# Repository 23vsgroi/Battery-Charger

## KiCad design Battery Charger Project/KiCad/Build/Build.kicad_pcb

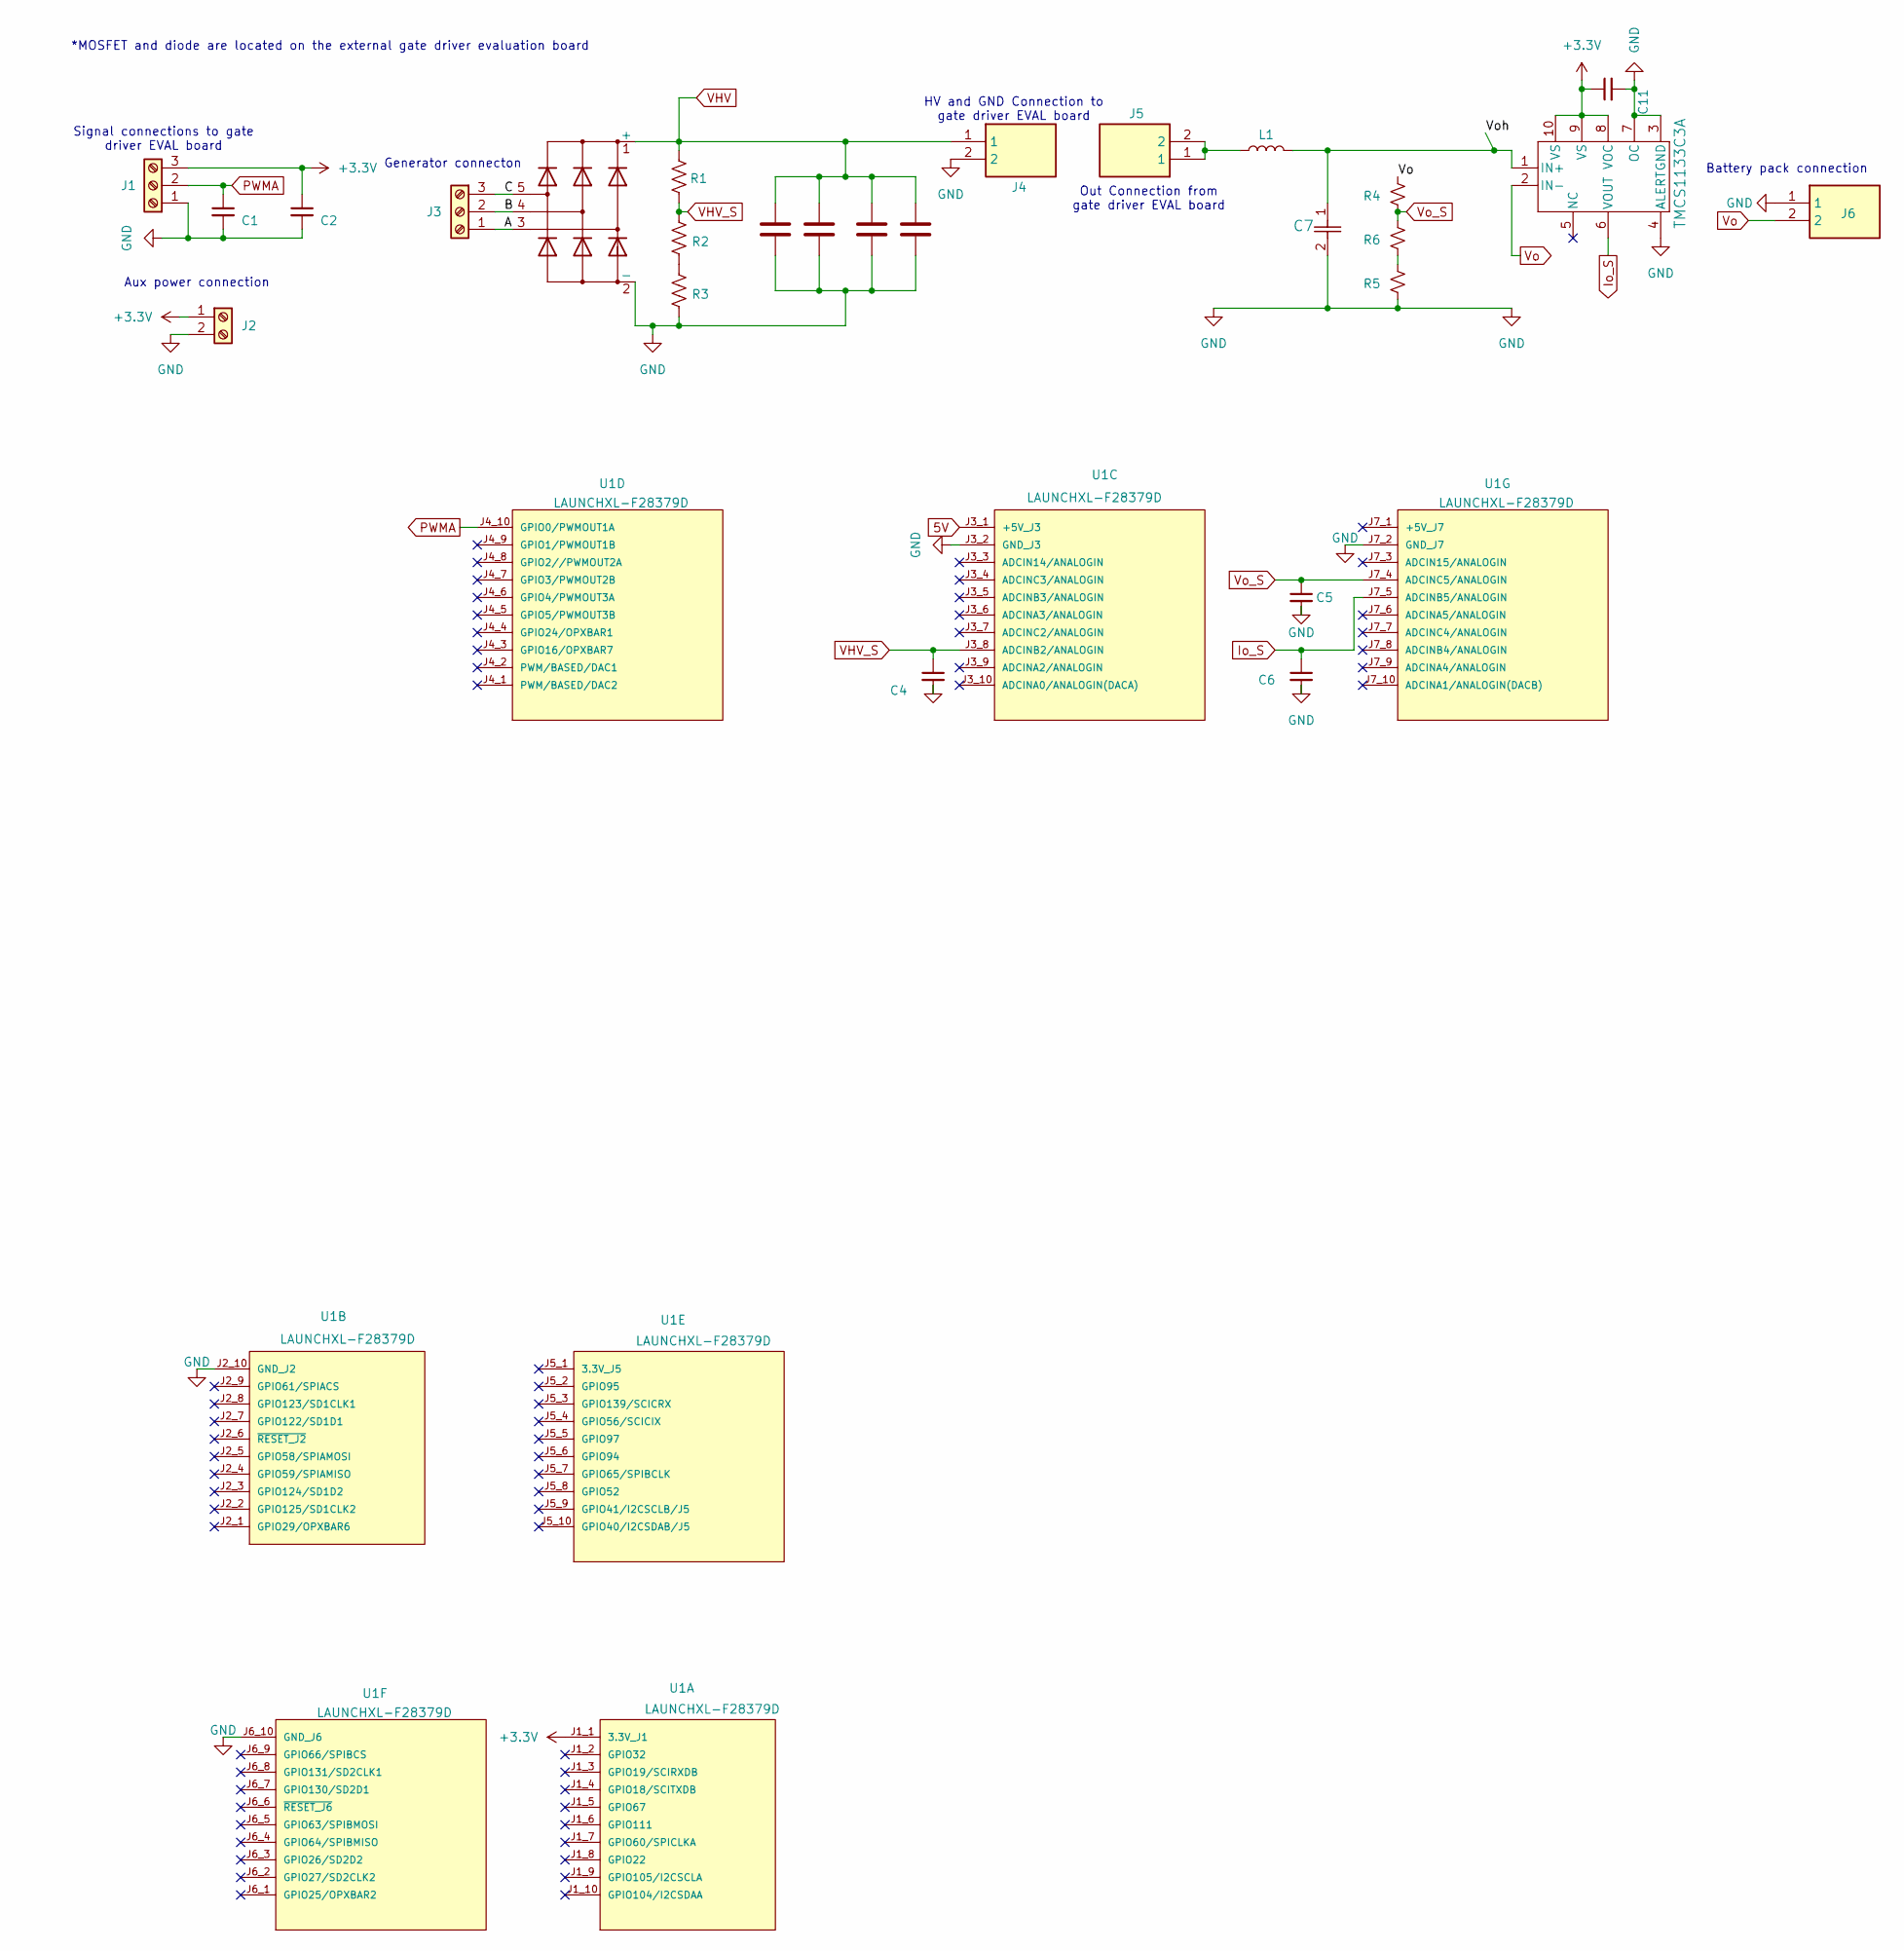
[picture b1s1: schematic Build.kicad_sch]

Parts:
C1, C2, C4, C5, C6, C11: C_Small; C_0805_2012Metric_Pad1.18x1.45mm_HandSolder
C3, C8, C9, C10: CAP_A30_NCH
C7: LLS2V821MELC; CAP_PAN_5X11_PAN
D1: DNA40U2200GU; DPF30U200FC
J1: Screw_Terminal_01x03; CONN3_284391-3_TEC
J2: Screw_Terminal_01x02; CONN2_284391-2_TEC
J3: Screw_Terminal_01x03; CONN_1935174_PXC
J4, J5, J6: 726386-2; CONN2_284391-2_TEC; Mouser Part Number 571-726386-2
L1: L; LC200-0185
R1: 300K; R_2010_5025Metric
R2: 6490; R_2010_5025Metric
R3: 36; R_2010_5025Metric
R4: 5K; R_2010_5025Metric
R5, R6: 680; R_2010_5025Metric
U1: LAUNCHXL-F28379D; PARTREV 2.0
U2: TMCS1133C3A; TMCS1133C5AQDVGR

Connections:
5V: U1.J3_1 (+5V_J3)
+3.3V: C2.1, C11.1, J1.3, J2.1, U1.J1_1 (3.3V_J1), U2.8 (VOC), U2.9 (VS), U2.10 (VS)
/A: D1.3, J3.1
/B: D1.4, J3.2
/C: D1.5, J3.3
/Voh: C7.1, L1.2, U2.1 (IN+)
GND: C1.2, C2.2, C3.2, C4.2, C5.2, C6.2, C7.2, C8.2, C9.2, C10.2, C11.2, D1.2 (-), J1.1, J2.2, J4.2, J6.1, R3.2, R5.2, U1.J2_10 (GND_J2), U1.J3_2 (GND_J3), U1.J6_10 (GND_J6), U1.J7_2 (GND_J7), U2.3 (GND), U2.4 (ALERT), U2.7 (OC)
Io_S: C6.1, U1.J7_5 (ADCINB5/ANALOGIN), U2.6 (VOUT)
unnamed: J5.1, J5.2, L1.1
unnamed: R2.2, R3.1
unnamed: R5.1, R6.2
PWMA: C1.1, J1.2, U1.J4_10 (GPIO0/PWMOUT1A)
VHV: C3.1, C8.1, C9.1, C10.1, D1.1 (+), J4.1, R1.1
VHV_S: C4.1, R1.2, R2.1, U1.J3_8 (ADCINB2/ANALOGIN)
Vo: J6.2, R4.1, U2.2 (IN-)
Vo_S: C5.1, R4.2, R6.1, U1.J7_4 (ADCINC5/ANALOGIN)

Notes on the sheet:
Aux power connection
Signal connections to gate driver EVAL board
Out Connection from gate driver EVAL board
Generator connecton
*MOSFET and diode are located on the external gate driver evaluation board
HV and GND Connection to gate driver EVAL board
Battery pack connection

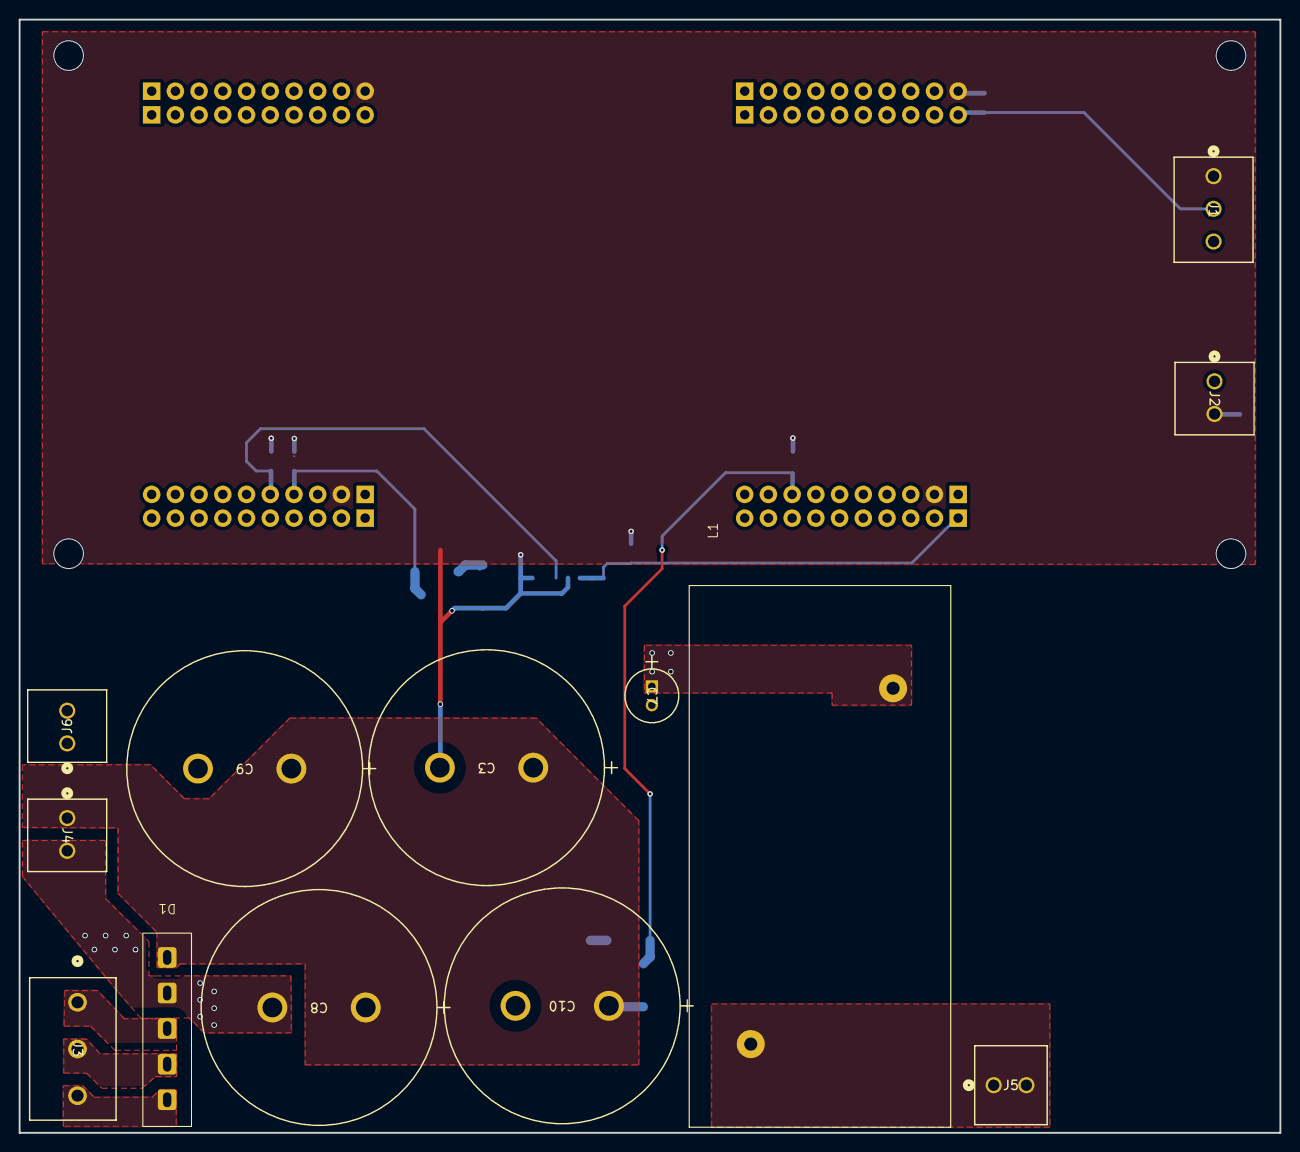
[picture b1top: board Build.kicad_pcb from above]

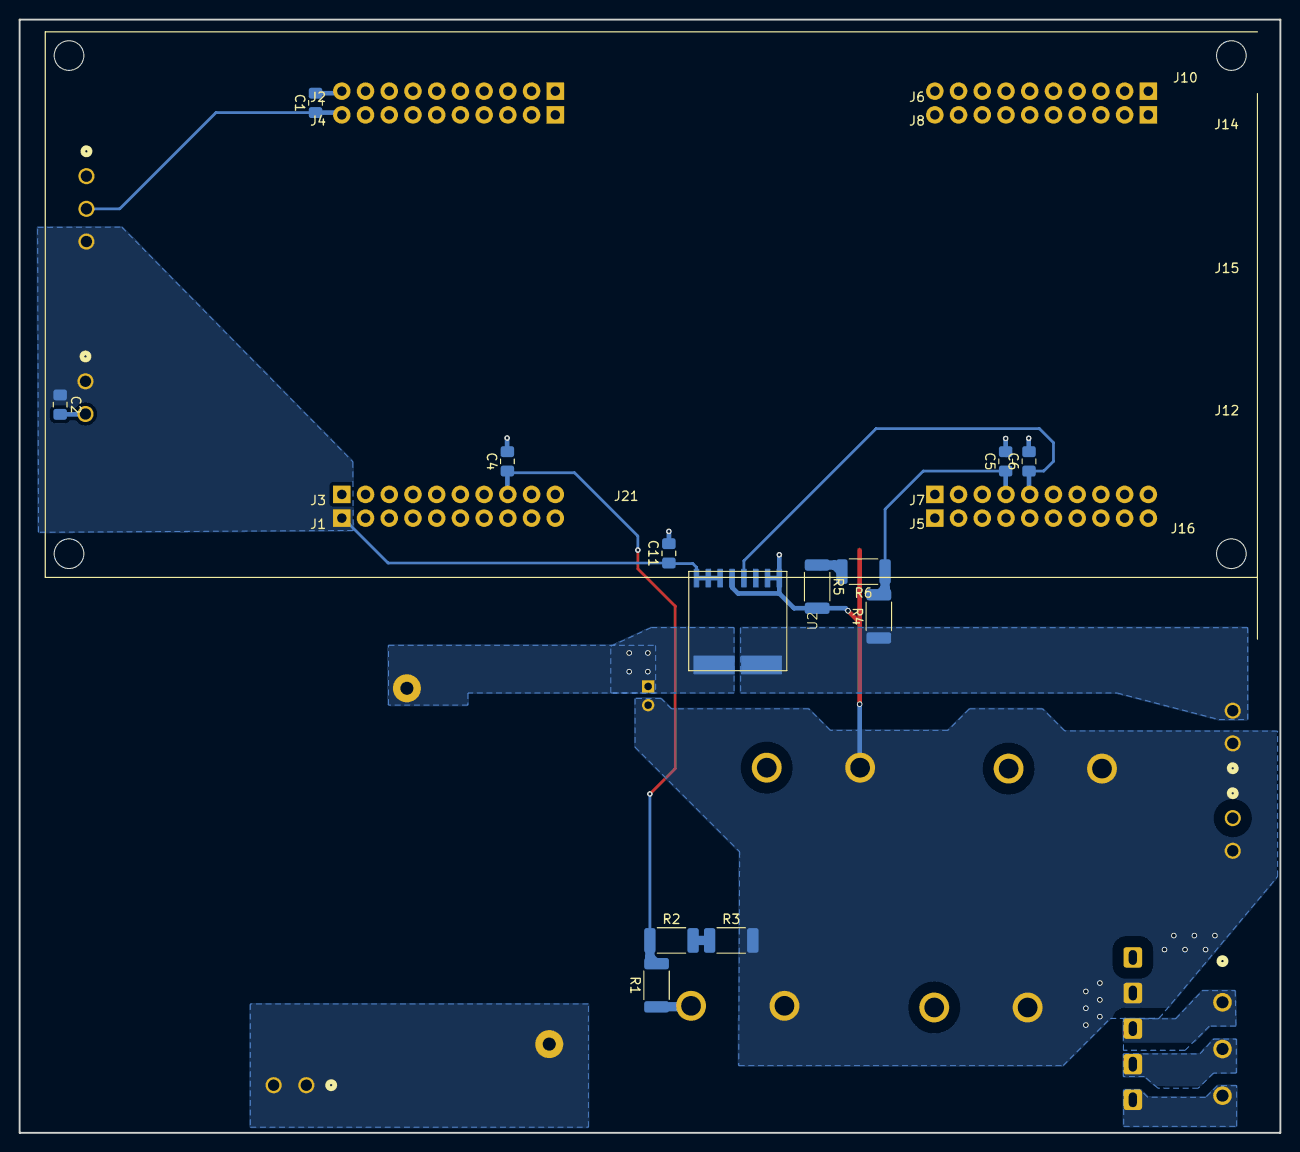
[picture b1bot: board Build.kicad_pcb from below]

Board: 2 copper layers, 135.0 x 119.2 mm, 27 parts (14 on the bottom side), 15 nets.

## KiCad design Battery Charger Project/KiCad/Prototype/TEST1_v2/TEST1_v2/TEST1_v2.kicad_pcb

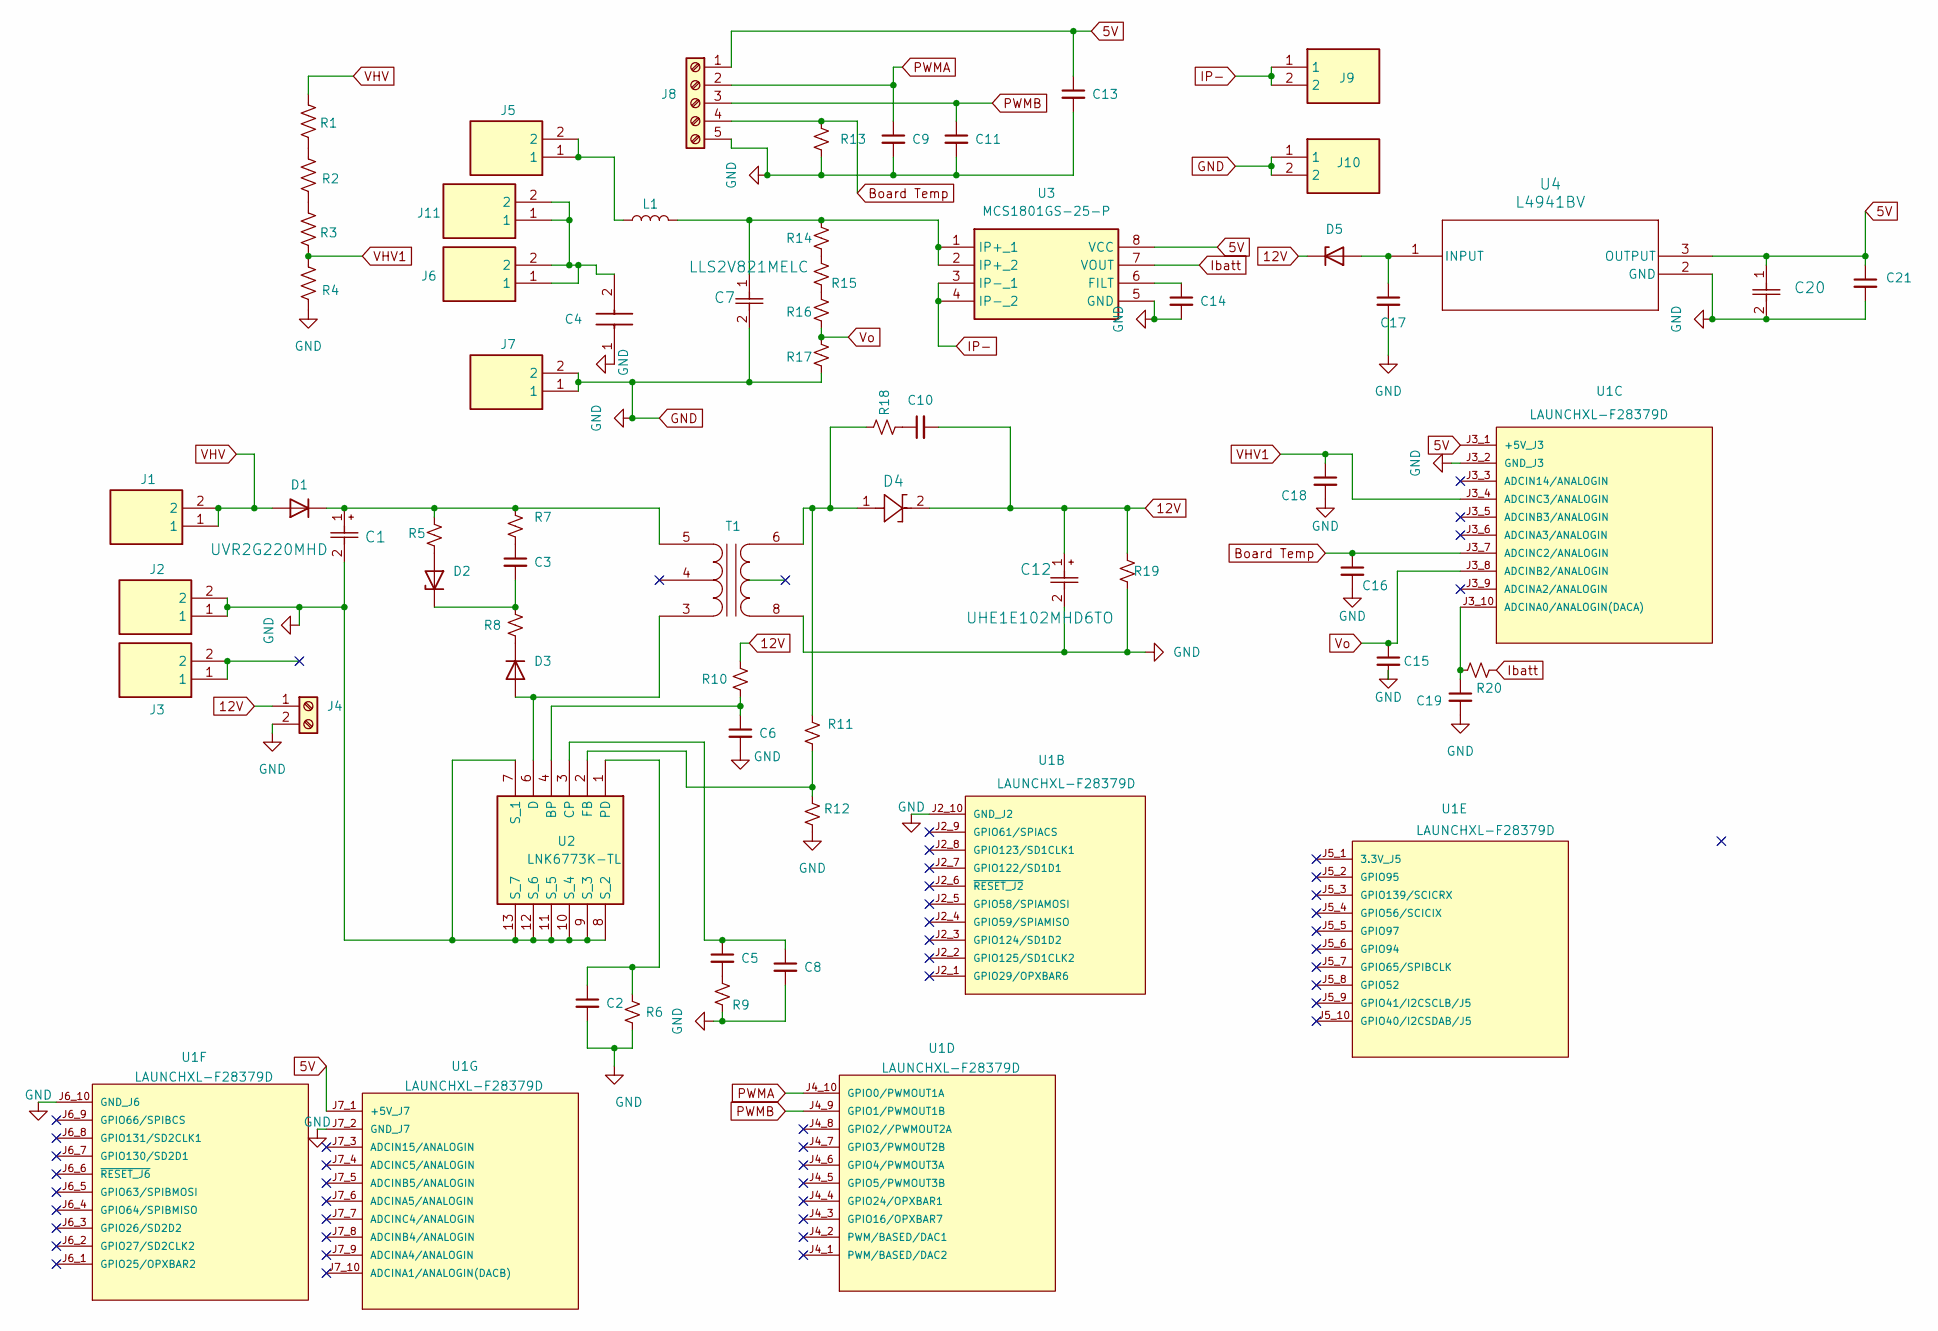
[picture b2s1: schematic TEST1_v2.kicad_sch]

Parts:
C1: UVR2G220MHD; CAP_UAQ_16X25_NCH
C2, C3, C10: C_Small; C_1206_3216Metric
C4: B32673P6225K000; B32673P__26.5_x_12_; Manufacturer_Part_Number B32673P6225K000; Mouser Part Number 871-B32673P6225K000
C5, C6, C8, C9, C11, C13, C14, C15, C16, C18, C19: C_Small; C_0805_2012Metric_Pad1.18x1.45mm_HandSolder
C7: LLS2V821MELC; CAP_C45_NCH
C12: UHE1E102MHD6TO; CAP_UAQ_12P5X20_NCH
C17, C21: 0.1uF; C_0805_2012Metric_Pad1.18x1.45mm_HandSolder
C20: CAP_WCAP-ATG5_05.0X11.0_WRE
D1, D3: US1M; D_SMA
D2, D5: D_Zener; D_SMA-SMB_Universal_Handsoldering
D4: STPS2H100U; SMB_STM
J1, J2, J3, J5, J6, J7, J9, J10, J11: 726386-2; Mouser Part Number 571-726386-2
J4: Screw_Terminal_01x02; TerminalBlock_bornier-2_P5.08mm
J8: Screw_Terminal_01x05; TerminalBlock_Phoenix_MPT-0,5-5-2.54_1x05_P2.54mm_Horizontal
L1: L; inductor_customized_v1
R1, R2, R3, R4: R_US; R_2010_5025Metric
R5, R7, R18, R20: R_Small_US; R_1206_3216Metric
R6, R9, R10, R14, R15, R16, R17: R_Small_US; R_2010_5025Metric
R8: R_Small_US; R_1206_3216Metric_Pad1.30x1.75mm_HandSolder
R11, R12, R19: R_Small_US; R_0805_2012Metric
R13: R_Small_US; R_0805_2012Metric_Pad1.20x1.40mm_HandSolder
T1: Transformer_SP_1S; Transformer_cust_v1
U1: LAUNCHXL-F28379D; MOD_LAUNCHXL-F28379D_v2; PARTREV 2.0
U2: LNK6773K-TL; LNK6773KTL; Mouser Part Number 869-LNK6773K-TL
U3: MCS1801GS-25-P; SOIC127P600X175-8N; Manufacturer_Part_Number MCS1801GS-25-P
U4: L4941BV; TO-220_STM

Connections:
5V: C13.1, C20.1, C21.1, J8.1, U1.J3_1 (+5V_J3), U1.J7_1 (+5V_J7), U3.8 (VCC), U4.3 (OUTPUT)
12V: C10.2, C12.1, D4.2, D5.1 (K), J4.1, R10.1, R19.1
Board Temp: C16.1, J8.4, R13.1, U1.J3_7 (ADCINC2/ANALOGIN)
GND: C1.2, C2.2, C4.1, C6.2, C7.2, C8.2, C9.2, C11.2, C12.2, C13.2, C14.2, C15.2, C16.2, C17.2, C18.2, C19.2, C20.2, C21.2, J2.1, J2.2, J4.2, J7.1, J7.2, J8.5, J10.1, J10.2, R4.2, R6.2, R9.2, R12.2, R13.2, R17.2, R19.2, T1.8 (S1), U1.J2_10 (GND_J2), U1.J3_2 (GND_J3), U1.J6_10 (GND_J6), U1.J7_2 (GND_J7), U2.7 (S_1), U2.8 (S_2), U2.9 (S_3), U2.10 (S_4), U2.11 (S_5), U2.12 (S_6), U2.13 (S_7), U3.5 (GND), U4.2 (GND)
IP-: J9.1, J9.2, U3.3 (IP-_1), U3.4 (IP-_2)
Ibatt: R20.2, U3.7 (VOUT)
unnamed: C3.1, R7.2
unnamed: C4.2, J6.1, J6.2, J11.1, J11.2
unnamed: C5.2, R9.1
unnamed: C10.1, R18.2
unnamed: C1.1, D1.1 (K), R5.1, R7.1, T1.5 (PR1)
unnamed: D2.2 (A), R5.2
unnamed: C3.2, D2.1 (K), R8.1
unnamed: D3.2 (A), T1.3 (PR2), U2.6 (D)
unnamed: D3.1 (K), R8.2
unnamed: C17.1, D5.2 (A), U4.1 (INPUT)
unnamed: J5.1, J5.2, L1.1
unnamed: R1.2, R2.1
unnamed: R2.2, R3.1
unnamed: R14.2, R15.1
unnamed: R15.2, R16.1
unnamed: D4.1, R11.1, R18.1, T1.6 (S2)
unnamed: C19.1, R20.1, U1.J3_10 (ADCINA0/ANALOGIN(DACA))
unnamed: C6.1, R10.2, U2.4 (BP)
unnamed: C5.1, C8.1, U2.3 (CP)
unnamed: R11.2, R12.1, U2.2 (FB)
unnamed: C2.1, R6.1, U2.1 (PD)
unnamed: C14.1, U3.6 (FILT)
unnamed: C7.1, L1.2, R14.1, U3.1 (IP+_1), U3.2 (IP+_2)
PWMA: C9.1, J8.2, U1.J4_10 (GPIO0/PWMOUT1A)
PWMB: C11.1, J8.3, U1.J4_9 (GPIO1/PWMOUT1B)
VHV: D1.2 (A), J1.1, J1.2, R1.1
VHV1: C18.1, R3.2, R4.1, U1.J3_4 (ADCINC3/ANALOGIN)
Vo: C15.1, R16.2, R17.1, U1.J3_8 (ADCINB2/ANALOGIN)

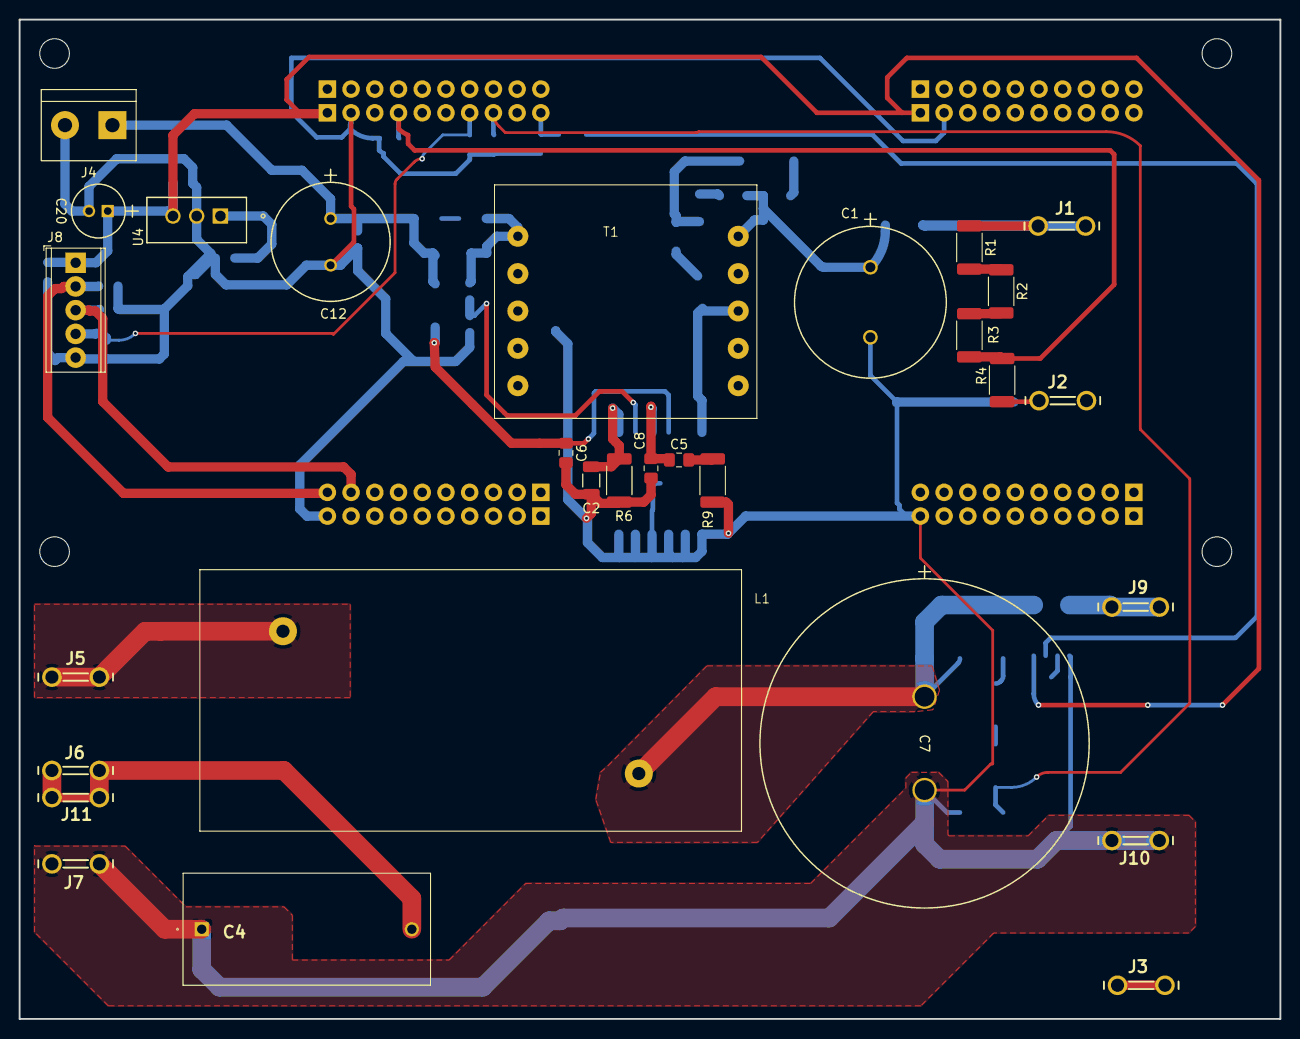
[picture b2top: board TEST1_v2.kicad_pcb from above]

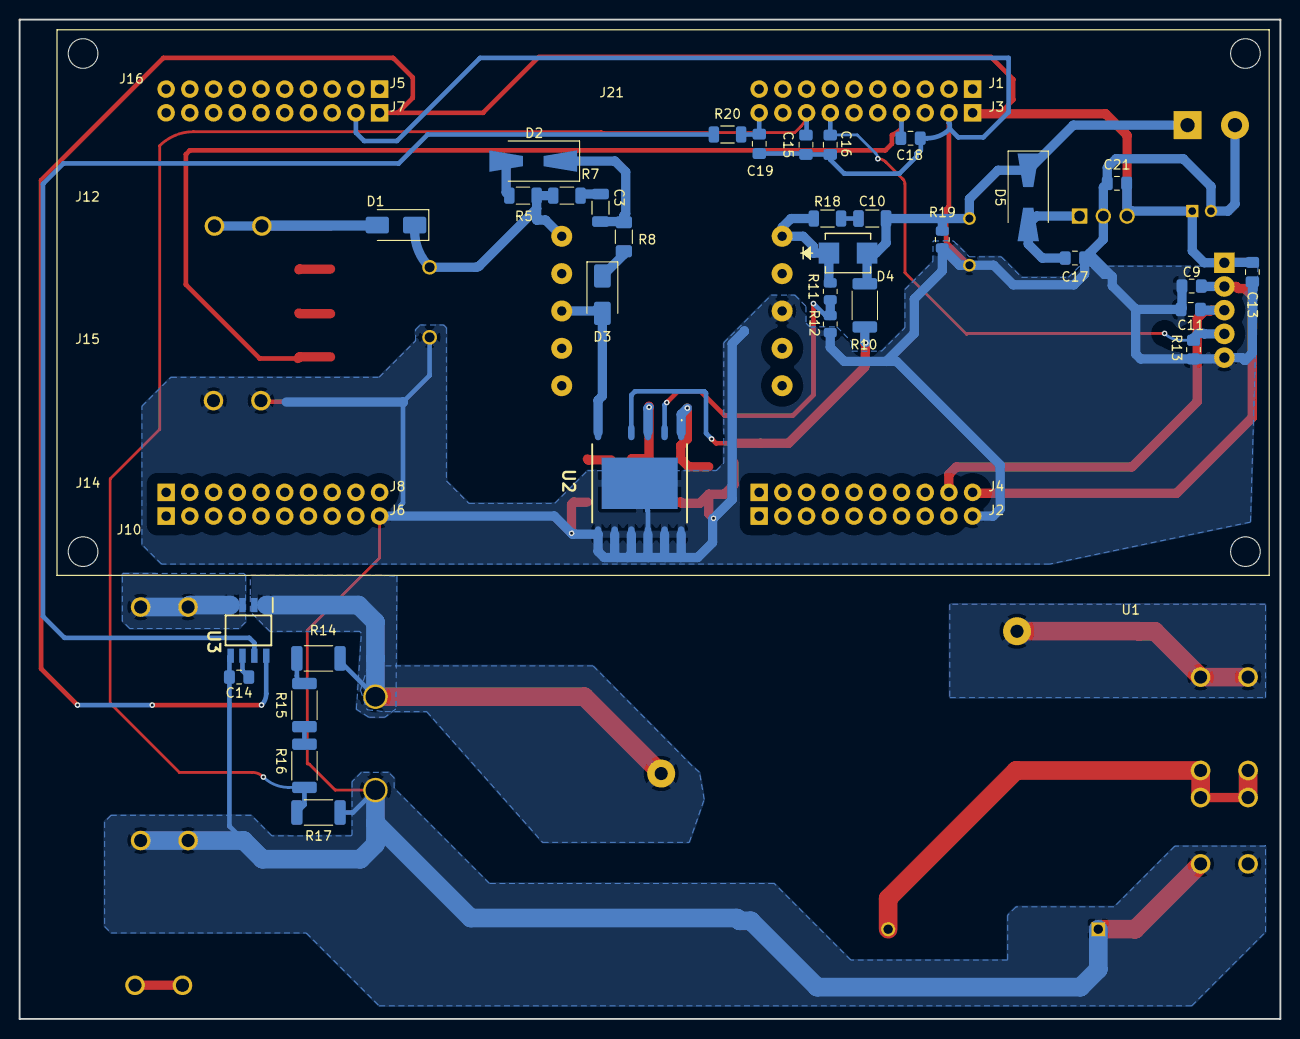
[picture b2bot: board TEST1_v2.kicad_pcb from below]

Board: 2 copper layers, 135.0 x 107.0 mm, 63 parts (34 on the bottom side), 34 nets.
